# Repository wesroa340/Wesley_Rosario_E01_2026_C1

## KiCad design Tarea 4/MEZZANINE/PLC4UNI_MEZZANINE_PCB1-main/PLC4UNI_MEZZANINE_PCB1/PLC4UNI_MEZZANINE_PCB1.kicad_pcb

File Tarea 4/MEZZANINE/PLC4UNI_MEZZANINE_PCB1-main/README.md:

# PLC4UNI_MEZZANINE_PCB1
Tarjeta PCB tipo Mezzanine del proyecto PLC4UNI

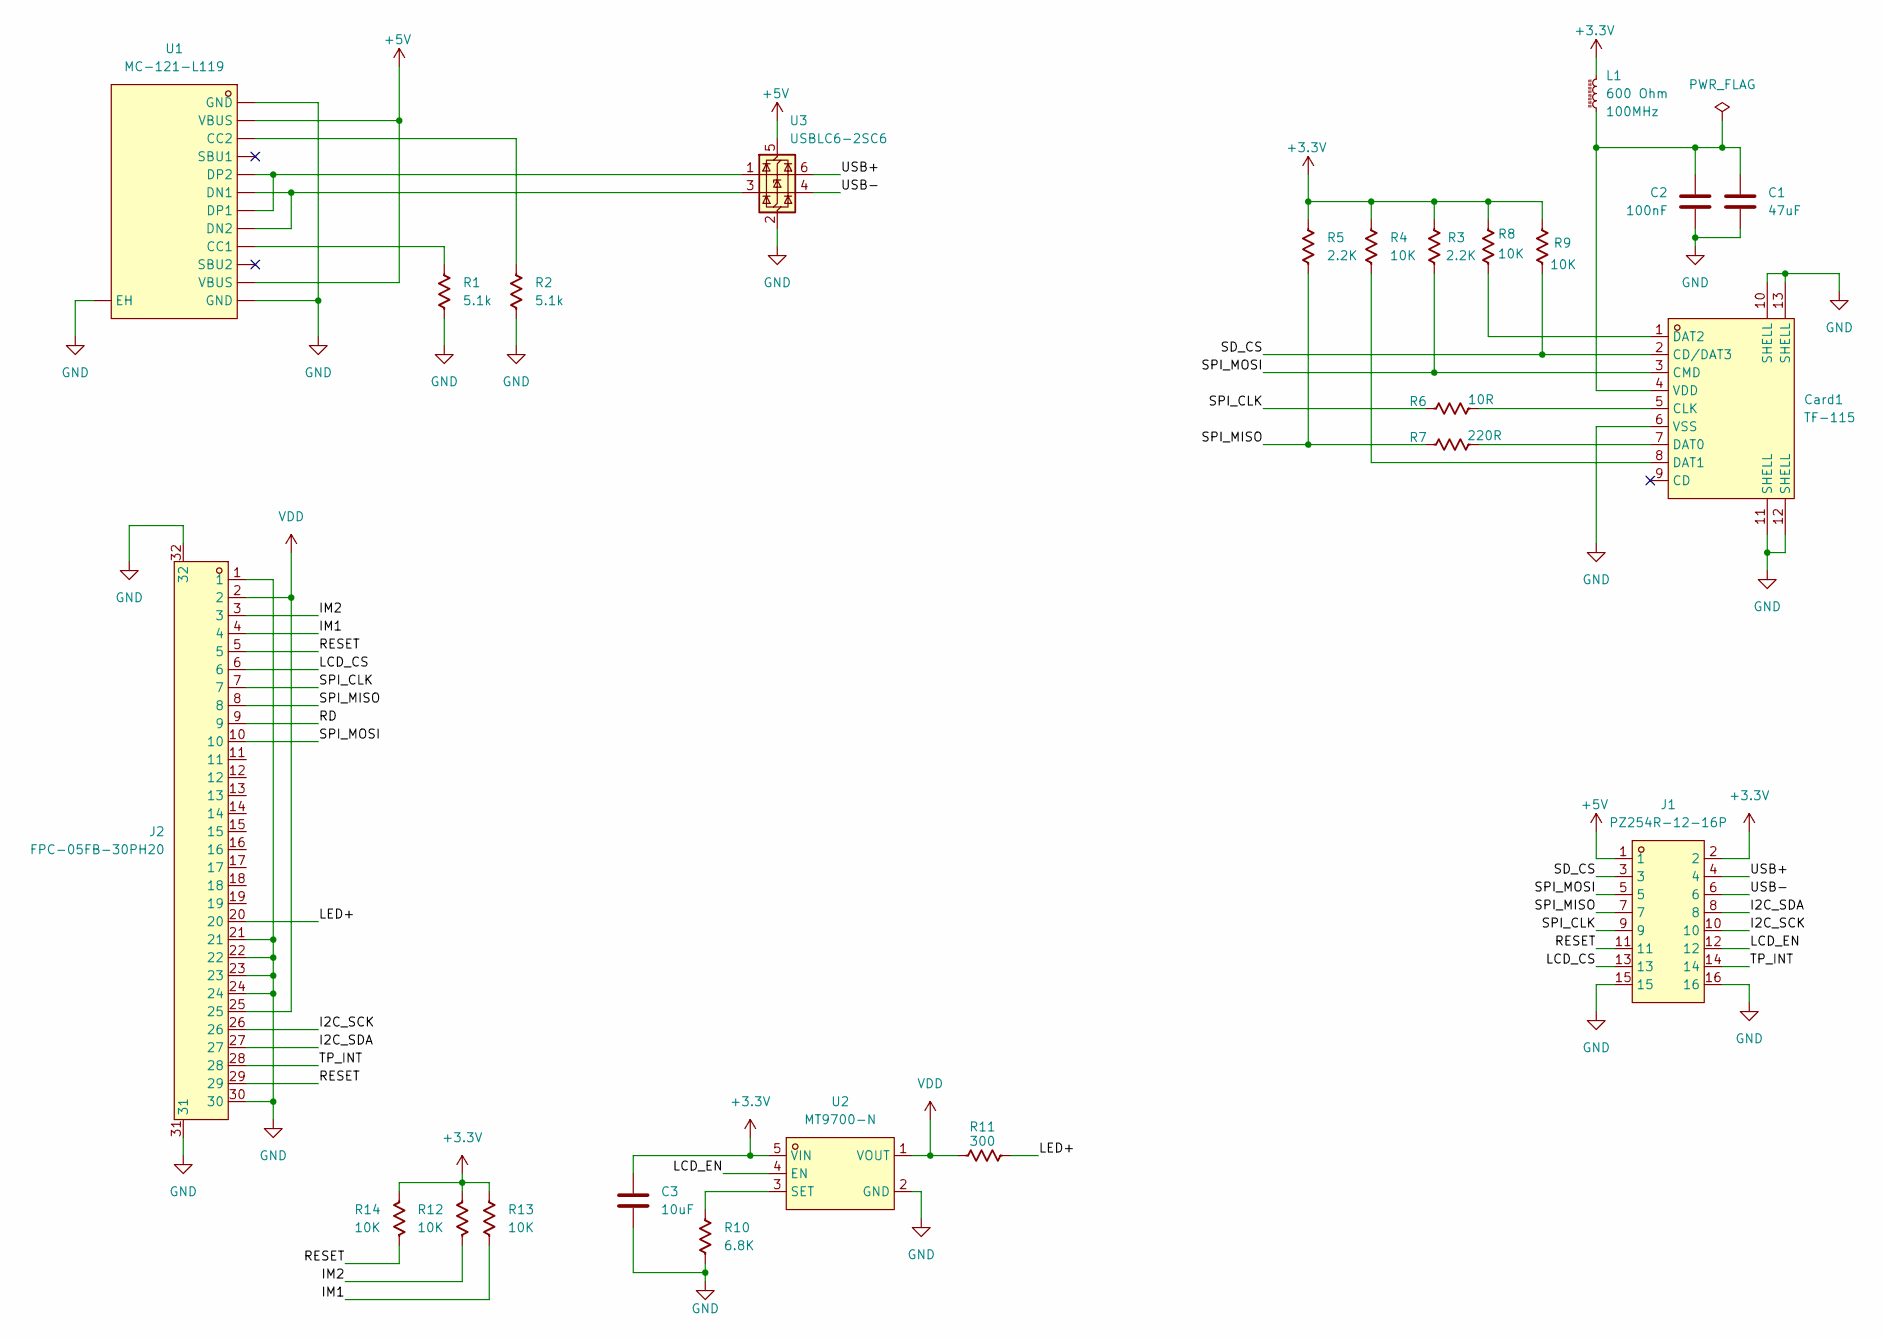
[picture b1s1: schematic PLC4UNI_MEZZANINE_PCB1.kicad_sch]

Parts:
C1: 47uF; C_0603_1608Metric
C2: 100nF; C_0603_1608Metric
C3: 10uF; C_0603_1608Metric
Card1: TF-115; TF-SMD_TF-115; LCSC Part C266620
J1: PZ254R-12-16P; HDR-TH_16P-P2.54-H-M-R2-C8-S2.54; LCSC Part C492436
J2: FPC-05FB-30PH20; FPC-SMD_30P-P0.50_FPC-05FB-30PH20; LCSC Part C2856833
L1: 600 Ohm; C_0805_2012Metric
R1, R2: 5.1k; R_0603_1608Metric
R3, R5: 2.2K; R_0603_1608Metric
R4, R8, R9, R12, R13, R14: 10K; R_0603_1608Metric
R6: 10R; R_0603_1608Metric
R7: 220R; R_0603_1608Metric
R10: 6.8K; R_0603_1608Metric
R11: 300; R_0603_1608Metric
U1: MC-121-L119; USB-C-SMD_HANBO_MC-121-L119; LCSC Part C6332278
U2: MT9700-N; SOT-23-5_L2.9-W1.6-P0.95-LS2.9-BL; LCSC Part C42441843
U3: USBLC6-2SC6; SOT-23-6

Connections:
+3.3V: C3.1, J1.2, L1.2, R3.1, R4.1, R5.1, R8.1, R9.1, R12.1, R13.1, R14.1, U2.5 (VIN)
+5V: J1.1, U1.A4B9 (VBUS), U1.B4A9 (VBUS), U3.5 (VBUS)
/I2C_SCK: J1.10, J2.26
/I2C_SDA: J1.8, J2.27
/IM1: J2.4, R13.2
/IM2: J2.3, R12.2
/LCD_CS: J1.13, J2.6
/LCD_EN: J1.12, U2.4 (EN)
/LED+: J2.20, R11.2
/RD: J2.9
/RESET: J1.11, J2.5, J2.29, R14.2
/SD_CS: Card1.2 (CD/DAT3), J1.3, R9.2
/SPI_CLK: J1.9, J2.7, R6.1
/SPI_MISO: J1.7, J2.8, R5.2, R7.1
/SPI_MOSI: Card1.3 (CMD), J1.5, J2.10, R3.2
/TP_INT: J1.14, J2.28
/USB+: J1.4, U3.6 (I/O1)
/USB-: J1.6, U3.4 (I/O2)
GND: C1.2, C2.2, C3.2, Card1.6 (VSS), Card1.10 (SHELL), Card1.11 (SHELL), Card1.12 (SHELL), Card1.13 (SHELL), J1.15, J1.16, J2.1, J2.21, J2.22, J2.23, J2.24, J2.30, J2.31, J2.32, R1.2, R2.2, R10.2, U1.13 (EH), U1.A1B12 (GND), U1.B1A12 (GND), U2.2 (GND), U3.2 (GND)
unnamed: Card1.5 (CLK), R6.2
unnamed: Card1.7 (DAT0), R7.2
unnamed: Card1.8 (DAT1), R4.2
unnamed: Card1.1 (DAT2), R8.2
unnamed: C1.1, C2.1, Card1.4 (VDD), L1.1
unnamed: R1.1, U1.A5 (CC1)
unnamed: R2.1, U1.B5 (CC2)
unnamed: U1.A7 (DN1), U1.B7 (DN2), U3.3 (I/O2)
unnamed: U1.A6 (DP1), U1.B6 (DP2), U3.1 (I/O1)
unnamed: R10.1, U2.3 (SET)
VDD: J2.2, J2.25, R11.1, U2.1 (VOUT)

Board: 2 copper layers, 24 parts (0 on the bottom side), 29 nets, no tracks yet.

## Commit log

2026-02-12 PLC actu
2026-02-12 case
2026-02-15 perpectiva
2026-03-22 PROGRESO de las tareas 1 y 2
2026-03-22 Progreso 1 y 2
2026-03-22 GRan progreso
